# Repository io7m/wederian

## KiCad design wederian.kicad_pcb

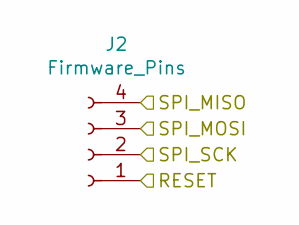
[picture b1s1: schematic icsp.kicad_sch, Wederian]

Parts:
J2: Firmware_Pins; PinSocket_1x04_P2.00mm_Vertical_SMD_Pin1Left

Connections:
/ICSP/RESET: J2.1; also elsewhere on the board
/ICSP/SPI_MISO: J2.4; also elsewhere on the board
/ICSP/SPI_MOSI: J2.3; also elsewhere on the board
/ICSP/SPI_SCK: J2.2; also elsewhere on the board

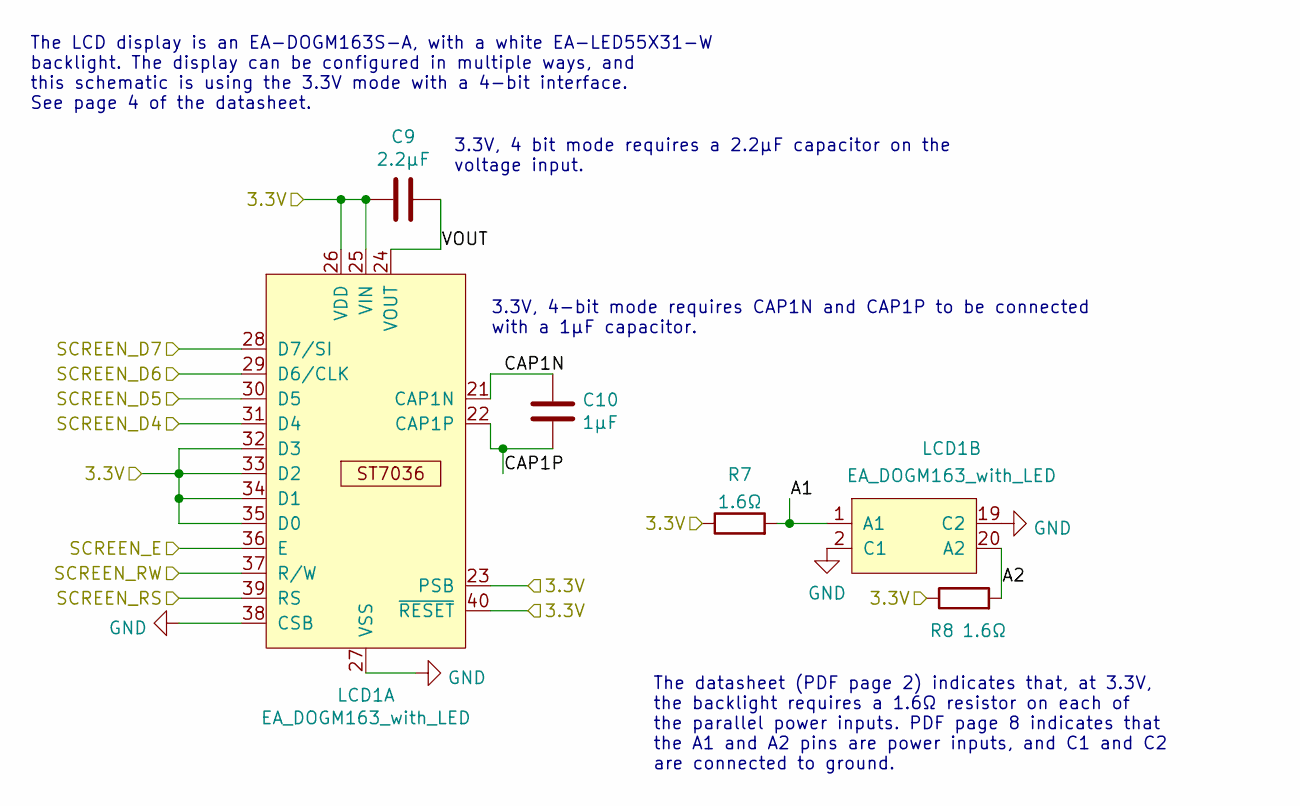
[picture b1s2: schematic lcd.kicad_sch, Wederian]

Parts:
C9: 2.2μF; C_0603_1608Metric
C10: 1μF; C_0603_1608Metric
LCD1: EA_DOGM163_with_LED; DOGM163_with_LED
R7, R8: 1.6Ω; R_0603_1608Metric

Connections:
/LCD/A1: LCD1.1 (A1), R7.2
/LCD/A2: LCD1.20 (A2), R8.2
/LCD/CAP1N: C10.1, LCD1.21 (CAP1N)
/LCD/CAP1P: C10.2, LCD1.22 (CAP1P)
/LCD/SCREEN_D4: LCD1.31 (D4); also elsewhere on the board
/LCD/SCREEN_D5: LCD1.30 (D5); also elsewhere on the board
/LCD/SCREEN_D6: LCD1.29 (D6/CLK); also elsewhere on the board
/LCD/SCREEN_D7: LCD1.28 (D7/SI); also elsewhere on the board
/LCD/SCREEN_E: LCD1.36 (E); also elsewhere on the board
/LCD/SCREEN_RS: LCD1.39 (RS); also elsewhere on the board
/LCD/SCREEN_RW: LCD1.37 (R/W); also elsewhere on the board
/LCD/VOUT: C9.2, LCD1.24 (VOUT)
/Power Regulation/VOUT: C9.1, LCD1.23 (PSB), LCD1.25 (VIN), LCD1.26 (VDD), LCD1.32 (D3), LCD1.33 (D2), LCD1.34 (D1), LCD1.35 (D0), LCD1.40 (~RESET), R7.1, R8.1; also elsewhere on the board
GND: LCD1.2 (C1), LCD1.19 (C2), LCD1.27 (VSS), LCD1.38 (CSB); also elsewhere on the board

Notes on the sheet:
The LCD display is an EA-DOGM163S-A, with a white EA-LED55X31-W backlight. The display can be configured in multiple ways, and this schematic is using the 3.3V mode with a 4-bit interface. See page 4 of the datasheet.
3.3V, 4 bit mode requires a 2.2μF capacitor on the voltage input.
3.3V, 4-bit mode requires CAP1N and CAP1P to be connected with a 1μF capacitor.
The datasheet (PDF page 2) indicates that, at 3.3V, the backlight requires a 1.6Ω resistor on each of the parallel power inputs. PDF page 8 indicates that the A1 and A2 pins are power inputs, and C1 and C2 are connected to ground.

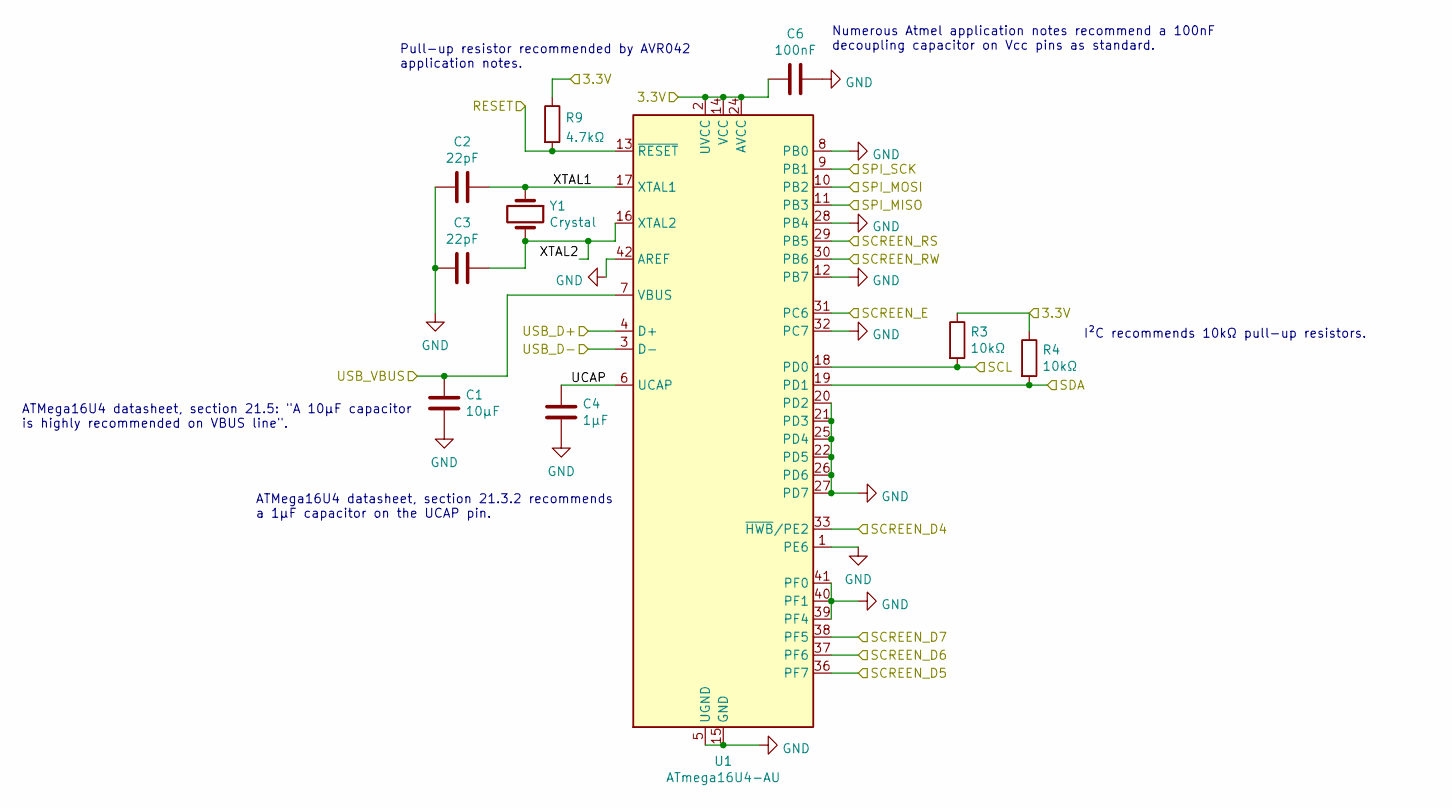
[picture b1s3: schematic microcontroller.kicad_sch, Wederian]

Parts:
C1: 10μF; C_0805_2012Metric
C2, C3: 22pF; C_0603_1608Metric
C4: 1μF; C_0603_1608Metric
C6: 100nF; C_0603_1608Metric
R3, R4: 10kΩ; R_0603_1608Metric
R9: 4.7kΩ; R_0603_1608Metric
U1: ATmega16U4-AU; TQFP-44_10x10mm_P0.8mm
Y1: Crystal; Crystal_SMD_HC49-SD

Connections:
/ICSP/RESET: R9.2, U1.13 (~RESET); also elsewhere on the board
/ICSP/SPI_MISO: U1.11 (PB3); also elsewhere on the board
/ICSP/SPI_MOSI: U1.10 (PB2); also elsewhere on the board
/ICSP/SPI_SCK: U1.9 (PB1); also elsewhere on the board
/LCD/SCREEN_D4: U1.33 (~HWB/PE2); also elsewhere on the board
/LCD/SCREEN_D5: U1.36 (PF7); also elsewhere on the board
/LCD/SCREEN_D6: U1.37 (PF6); also elsewhere on the board
/LCD/SCREEN_D7: U1.38 (PF5); also elsewhere on the board
/LCD/SCREEN_E: U1.31 (PC6); also elsewhere on the board
/LCD/SCREEN_RS: U1.29 (PB5); also elsewhere on the board
/LCD/SCREEN_RW: U1.30 (PB6); also elsewhere on the board
/Microcontroller/SCL: R3.2, U1.18 (PD0); also elsewhere on the board
/Microcontroller/SDA: R4.2, U1.19 (PD1); also elsewhere on the board
/Microcontroller/UCAP: C4.1, U1.6 (UCAP)
/Microcontroller/USB_D+: U1.4 (D+); also elsewhere on the board
/Microcontroller/USB_D-: U1.3 (D-); also elsewhere on the board
/Microcontroller/USB_VBUS: C1.1, U1.7 (VBUS); also elsewhere on the board
/Microcontroller/XTAL1: C2.1, U1.17 (XTAL1), Y1.1
/Microcontroller/XTAL2: C3.1, U1.16 (XTAL2), Y1.2
/Power Regulation/VOUT: C6.2, R3.1, R4.1, R9.1, U1.2 (UVCC), U1.14 (VCC), U1.24 (AVCC), U1.34 (VCC), U1.44 (AVCC); also elsewhere on the board
GND: C1.2, C2.2, C3.2, C4.2, C6.1, U1.1 (PE6), U1.5 (UGND), U1.8 (PB0), U1.12 (PB7), U1.15 (GND), U1.20 (PD2), U1.21 (PD3), U1.22 (PD5), U1.23 (GND), U1.25 (PD4), U1.26 (PD6), U1.27 (PD7), U1.28 (PB4), U1.32 (PC7), U1.35 (GND), U1.39 (PF4), U1.40 (PF1), U1.41 (PF0), U1.42 (AREF), U1.43 (GND); also elsewhere on the board

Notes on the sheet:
ATMega16U4 datasheet, section 21.5: "A 10μF capacitor is highly recommended on VBUS line".
ATMega16U4 datasheet, section 21.3.2 recommends a 1μF capacitor on the UCAP pin.
Pull-up resistor recommended by AVR042 application notes.
Numerous Atmel application notes recommend a 100nF decoupling capacitor on Vcc pins as standard.
I²C recommends 10kΩ pull-up resistors.

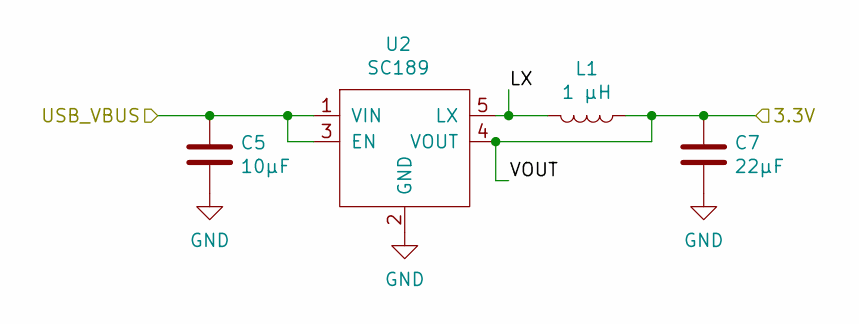
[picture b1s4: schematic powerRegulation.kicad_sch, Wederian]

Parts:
C5: 10μF; C_0805_2012Metric
C7: 22μF; C_0805_2012Metric
L1: 1 μH; L_0805_2012Metric
U2: SC189; SOT-23-5

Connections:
/Microcontroller/USB_VBUS: C5.1, U2.1 (VIN), U2.3 (EN); also elsewhere on the board
/Power Regulation/LX: L1.2, U2.5 (LX)
/Power Regulation/VOUT: C7.1, L1.1, U2.4 (VOUT); also elsewhere on the board
GND: C5.2, C7.2, U2.2 (GND); also elsewhere on the board

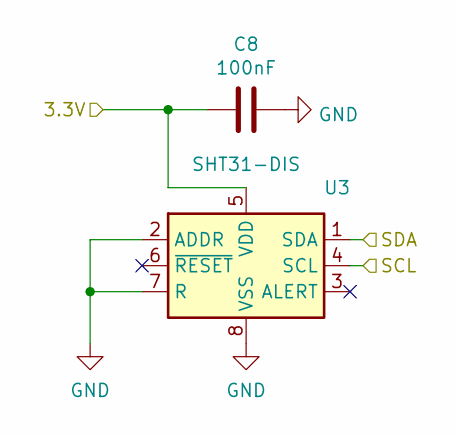
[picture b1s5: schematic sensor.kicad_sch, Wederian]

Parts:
C8: 100nF; C_0603_1608Metric
U3: SHT31-DIS; Sensirion_DFN-8-1EP_2.5x2.5mm_P0.5mm_EP1.1x1.7mm

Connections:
/Microcontroller/SCL: U3.4 (SCL); also elsewhere on the board
/Microcontroller/SDA: U3.1 (SDA); also elsewhere on the board
/Power Regulation/VOUT: C8.1, U3.5 (VDD); also elsewhere on the board
GND: C8.2, U3.2 (ADDR), U3.7 (R), U3.8 (VSS), U3.9 (VSS); also elsewhere on the board

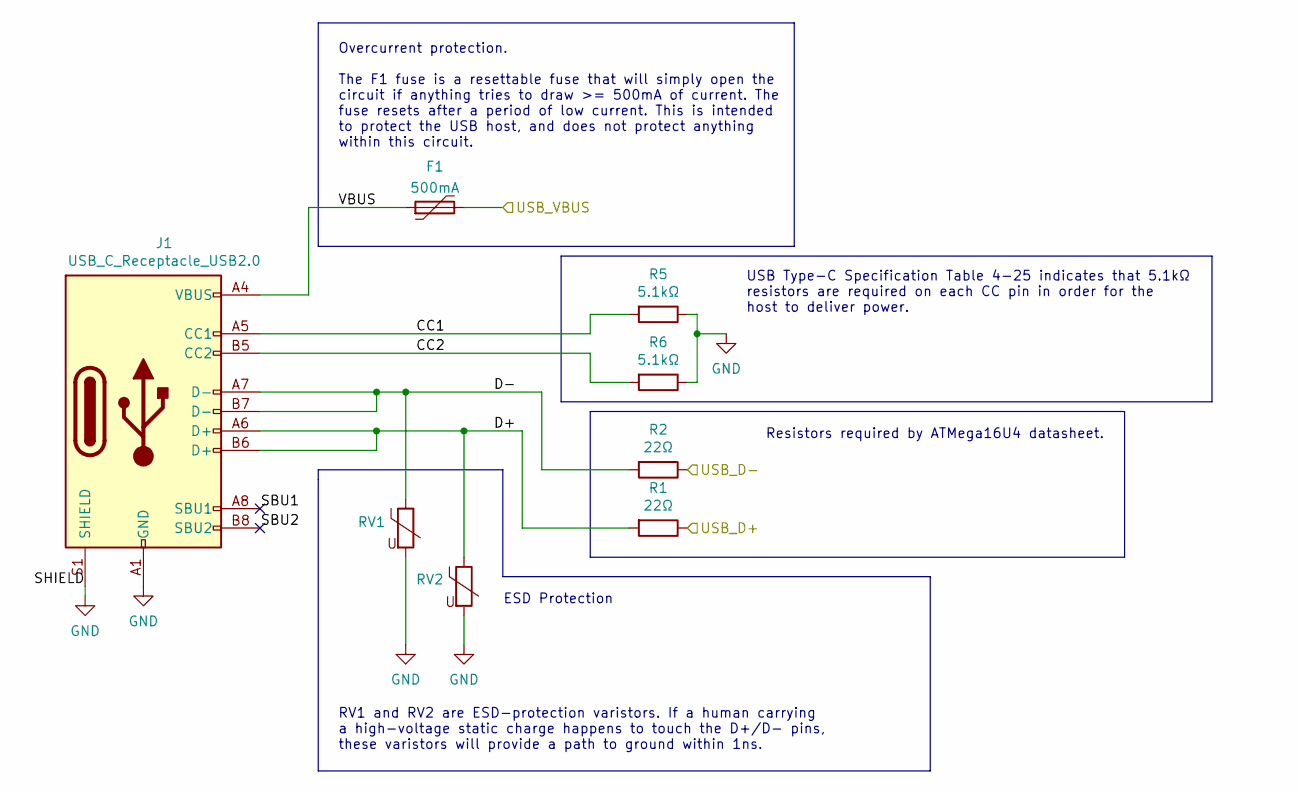
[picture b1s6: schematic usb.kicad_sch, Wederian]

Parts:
F1: 500mA; Fuse_1812_4532Metric
J1: USB_C_Receptacle_USB2.0; USB_C_Receptacle_Amphenol_12401610E4-2A
R1, R2: 22Ω; R_0603_1608Metric
R5, R6: 5.1kΩ; R_0603_1608Metric
RV1, RV2: CG0603MLC-05E; R_0603_1608Metric

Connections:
/Microcontroller/USB_D+: R1.1; also elsewhere on the board
/Microcontroller/USB_D-: R2.1; also elsewhere on the board
/Microcontroller/USB_VBUS: F1.2; also elsewhere on the board
/USB/CC1: J1.A5 (CC1), R5.2
/USB/CC2: J1.B5 (CC2), R6.2
/USB/D+: J1.A6 (D+), J1.B6 (D+), R1.2, RV2.1
/USB/D-: J1.A7 (D-), J1.B7 (D-), R2.2, RV1.1
/USB/SBU1: J1.A8 (SBU1)
/USB/SBU2: J1.B8 (SBU2)
/USB/VBUS: F1.1, J1.A4 (VBUS), J1.A9 (VBUS), J1.B4 (VBUS), J1.B9 (VBUS)
GND: J1.A1 (GND), J1.A12 (GND), J1.B1 (GND), J1.B12 (GND), J1.S1 (SHIELD), R5.1, R6.1, RV1.2, RV2.2; also elsewhere on the board

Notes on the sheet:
Overcurrent protection. The F1 fuse is a resettable fuse that will simply open the circuit if anything tries to draw >= 500mA of current. The fuse resets after a period of low current. This is intended to protect the USB host, and does not protect anything within this circuit.
RV1 and RV2 are ESD-protection varistors. If a human carrying a high-voltage static charge happens to touch the D+/D- pins, these varistors will provide a path to ground within 1ns.
ESD Protection
USB Type-C Specification Table 4-25 indicates that 5.1kΩ resistors are required on each CC pin in order for the host to deliver power.
Resistors required by ATMega16U4 datasheet.

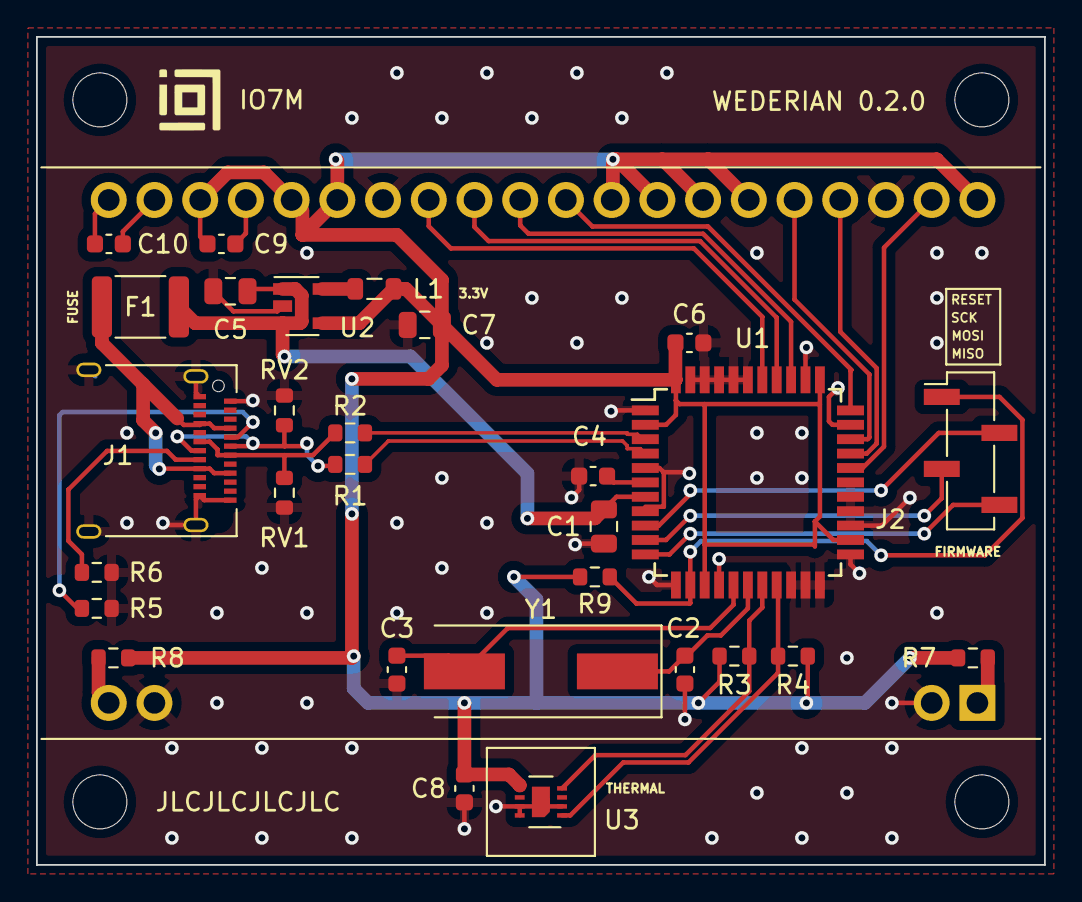
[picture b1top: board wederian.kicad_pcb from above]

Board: 2 copper layers, 56.0 x 46.0 mm, 30 parts (1 on the bottom side), 32 nets.

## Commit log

2021-10-24 Initial version
2021-10-24 Correctly set sheet pin directions
